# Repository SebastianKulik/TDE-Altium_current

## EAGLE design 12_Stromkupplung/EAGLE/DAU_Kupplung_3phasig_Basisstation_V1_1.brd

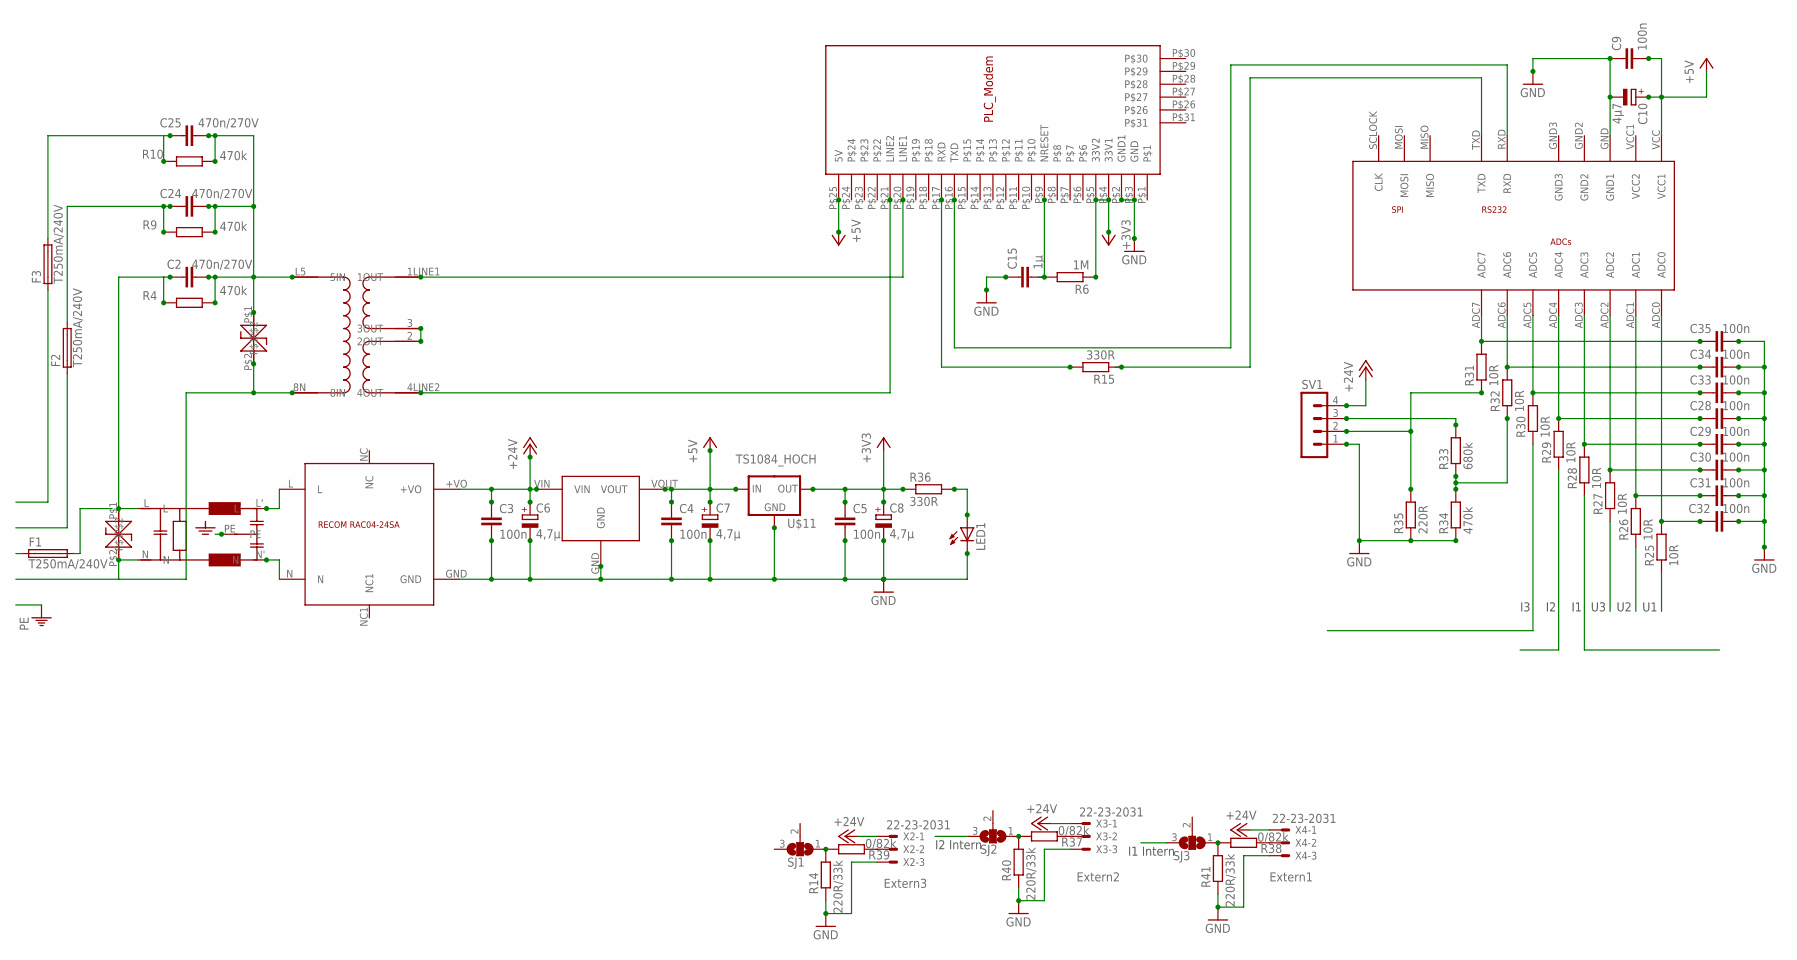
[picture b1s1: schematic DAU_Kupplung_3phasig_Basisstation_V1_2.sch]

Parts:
C2, C24, C25: 470n/270V; C225-087X268
C3, C4, C5, C9, C28, C29, C30, C31, C32, C33, C34, C35: 100n; C0805K
C6, C7, C8: 4,7µ; E2,5-6
C10: 4µ7; E2,5-6E
C15: 1µ; C0805K
F1, F2, F3: T250mA/240V; TR5
LED1: LEDSQR2X5; LED2X5
P6KE300CA: P6KE300CA; TSV
R4, R9, R10: 470k; 0204/7
R6: 1M; R0805
R14, R40, R41: 220R/33k; R0805
R15, R36: 330R; R0805
R25, R26, R27, R28, R29, R30, R31, R32: 10R; R0805
R33: 680k; R0805
R34: 470k; R0805
R35: 220R; R0805
R37, R38, R39: 0/82k; R0805
SJ1, SJ2, SJ3: SJ2WW; SJ_2W
SV1: MA04-1
TSV2: TSV
U$1: RECOM_RAC04_24SA; RAC04_12SA
U$3: ADUC831_MINIMUM; ADUC_MINIMUM
U$4: MODEMSTECKER; MODEM_FUSS
U$5: PLC_UEBERTRAGER_V2; PLC-UEBERTRAGER_V2
U$10: RECOM_785_05; RECOM785X
U$11: TS1084_HOCH
U$20: NETZFILTER_05_A; NETZFILTER
X2, X3, X4: 22-23-2031

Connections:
+3V3: C5.1, C8.+, R6.1, R36.1, U$4.P$4 (33V1), U$4.P$5 (33V2), U$11.OUT
+5V: C4.1, C7.+, C9.2, C10.+, U$3.VCC (VCC1), U$4.P$25 (5V), U$10.VOUT, U$11.IN
+12V: C3.1, C6.+, SV1.4, U$1.+VO, U$10.VIN, X2.1, X3.1, X4.1
ADC0: C32.1, R25.2, U$3.ADC0
ADC1: C31.1, R26.2, U$3.ADC1
ADC2: C30.1, R27.2, U$3.ADC2
ADC3: C29.1, R28.2, U$3.ADC3
ADC4: C28.1, R29.2, U$3.ADC4
ADC5: C33.1, R30.2, U$3.ADC5
GND: C3.2, C4.2, C5.2, C6.-, C7.-, C8.-, C9.1, C10.-, C15.1, C28.2, C29.2, C30.2, C31.2, C32.2, C33.2, C34.2, C35.2, LED1.K (C), R14.1, R34.1, R35.1, R40.1, R41.1, SV1.1, U$1.GND, U$3.GND (GND1), U$4.P$2 (GND1), U$4.P$3 (GND), U$10.GND, U$11.GND, X2.3, X3.3, X4.3
I1: R28.1, SJ3.2
I1INTERN: SJ3.3
I2: R29.1, SJ2.2
I2INTERN: SJ2.3
I3: R30.1, SJ1.2
L1: C2.1, F1.2, P6KE300CA.P$1, R4.2, U$20.L
L2: C24.1, F2.2, R9.2
L3: C25.1, F3.2, R10.2
N: P6KE300CA.P$2, TSV2.P$2, U$5.8N (8IN), U$20.N
unnamed: R15.2, U$4.P$17 (RXD)
unnamed: U$4.P$20 (LINE1), U$5.1LINE1 (1OUT)
unnamed: C35.1, R31.2, U$3.ADC7
unnamed: U$4.P$21 (LINE2), U$5.4LINE2 (4OUT)
unnamed: R15.1, U$3.TXD
unnamed: U$3.RXD, U$4.P$16 (TXD)
unnamed: U$1.L, U$20.L'
unnamed: LED1.A, R36.2
unnamed: C15.2, R6.2, U$4.P$9 (NRESET)
unnamed: C34.1, R32.2, U$3.ADC6
unnamed: C2.2, C24.2, C25.2, R4.1, R9.1, R10.1, TSV2.P$1, U$5.L5 (5IN)
unnamed: U$5.2 (2OUT), U$5.3 (3OUT)
unnamed: R33.2, SV1.3
unnamed: U$1.N, U$20.N'
unnamed: R37.2, R40.2, SJ2.1
unnamed: R37.1, X3.2
unnamed: R14.2, R39.2, SJ1.1
unnamed: R32.1, R33.1, R34.2
unnamed: R31.1, R35.2, SV1.2
unnamed: R39.1, X2.2
unnamed: R38.2, R41.2, SJ3.1
unnamed: R38.1, X4.2
PE: U$20.PE
U1: R25.1
U2: R26.1
U3: R27.1

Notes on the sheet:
Extern1
Extern2
Extern3
I1 Intern
I2 Intern

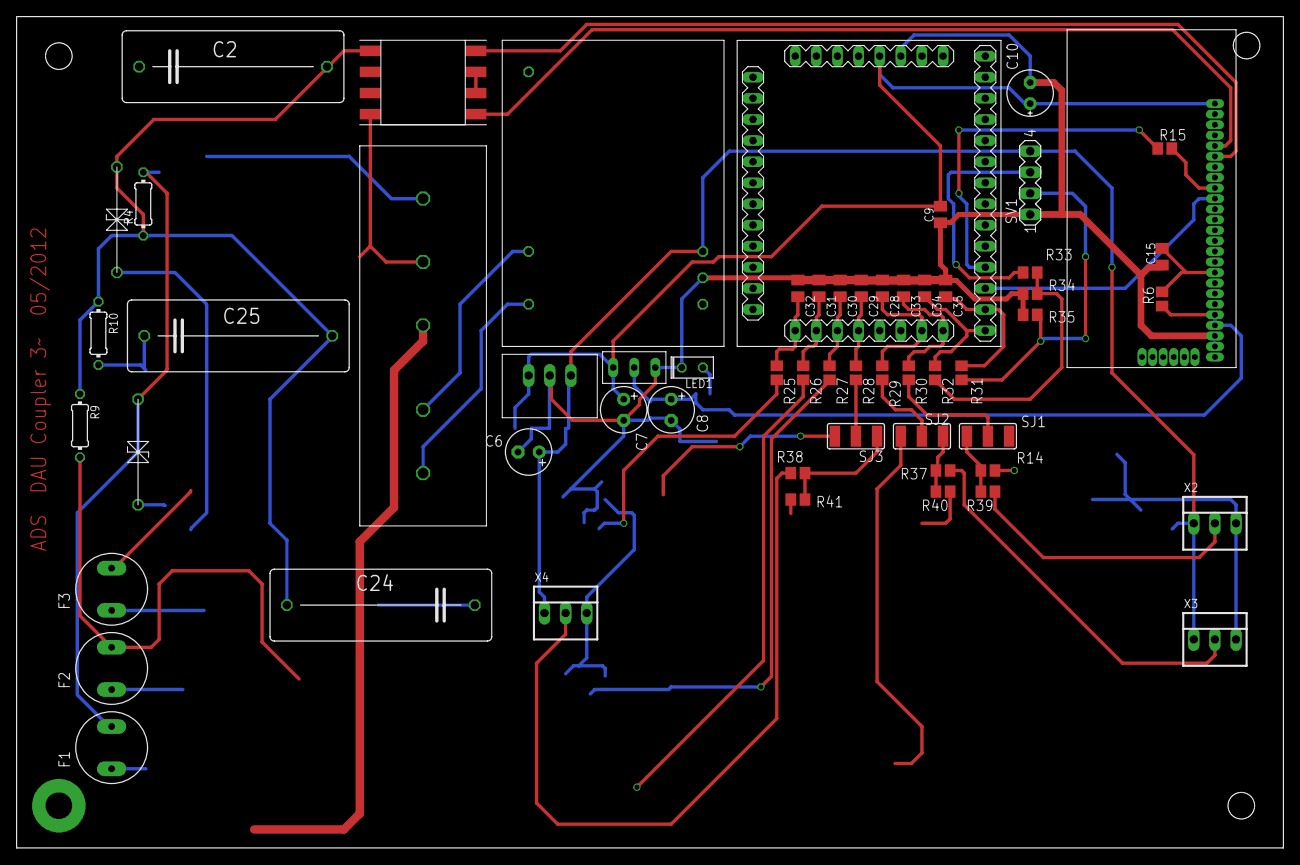
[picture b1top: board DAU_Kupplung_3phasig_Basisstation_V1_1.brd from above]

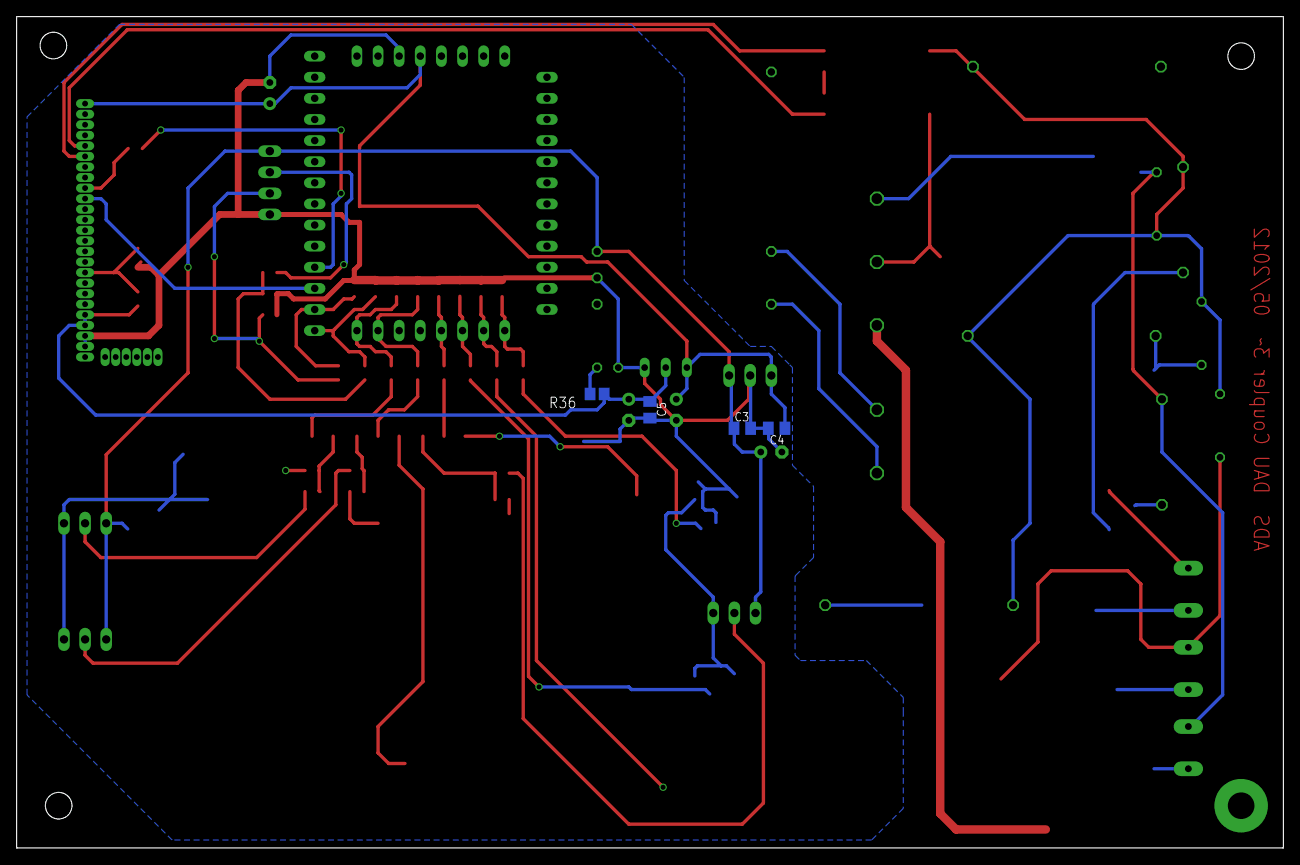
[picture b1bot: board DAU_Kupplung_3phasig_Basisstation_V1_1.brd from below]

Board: 2 copper layers, 152.4 x 100.0 mm, 63 parts (4 on the bottom side), 39 nets.

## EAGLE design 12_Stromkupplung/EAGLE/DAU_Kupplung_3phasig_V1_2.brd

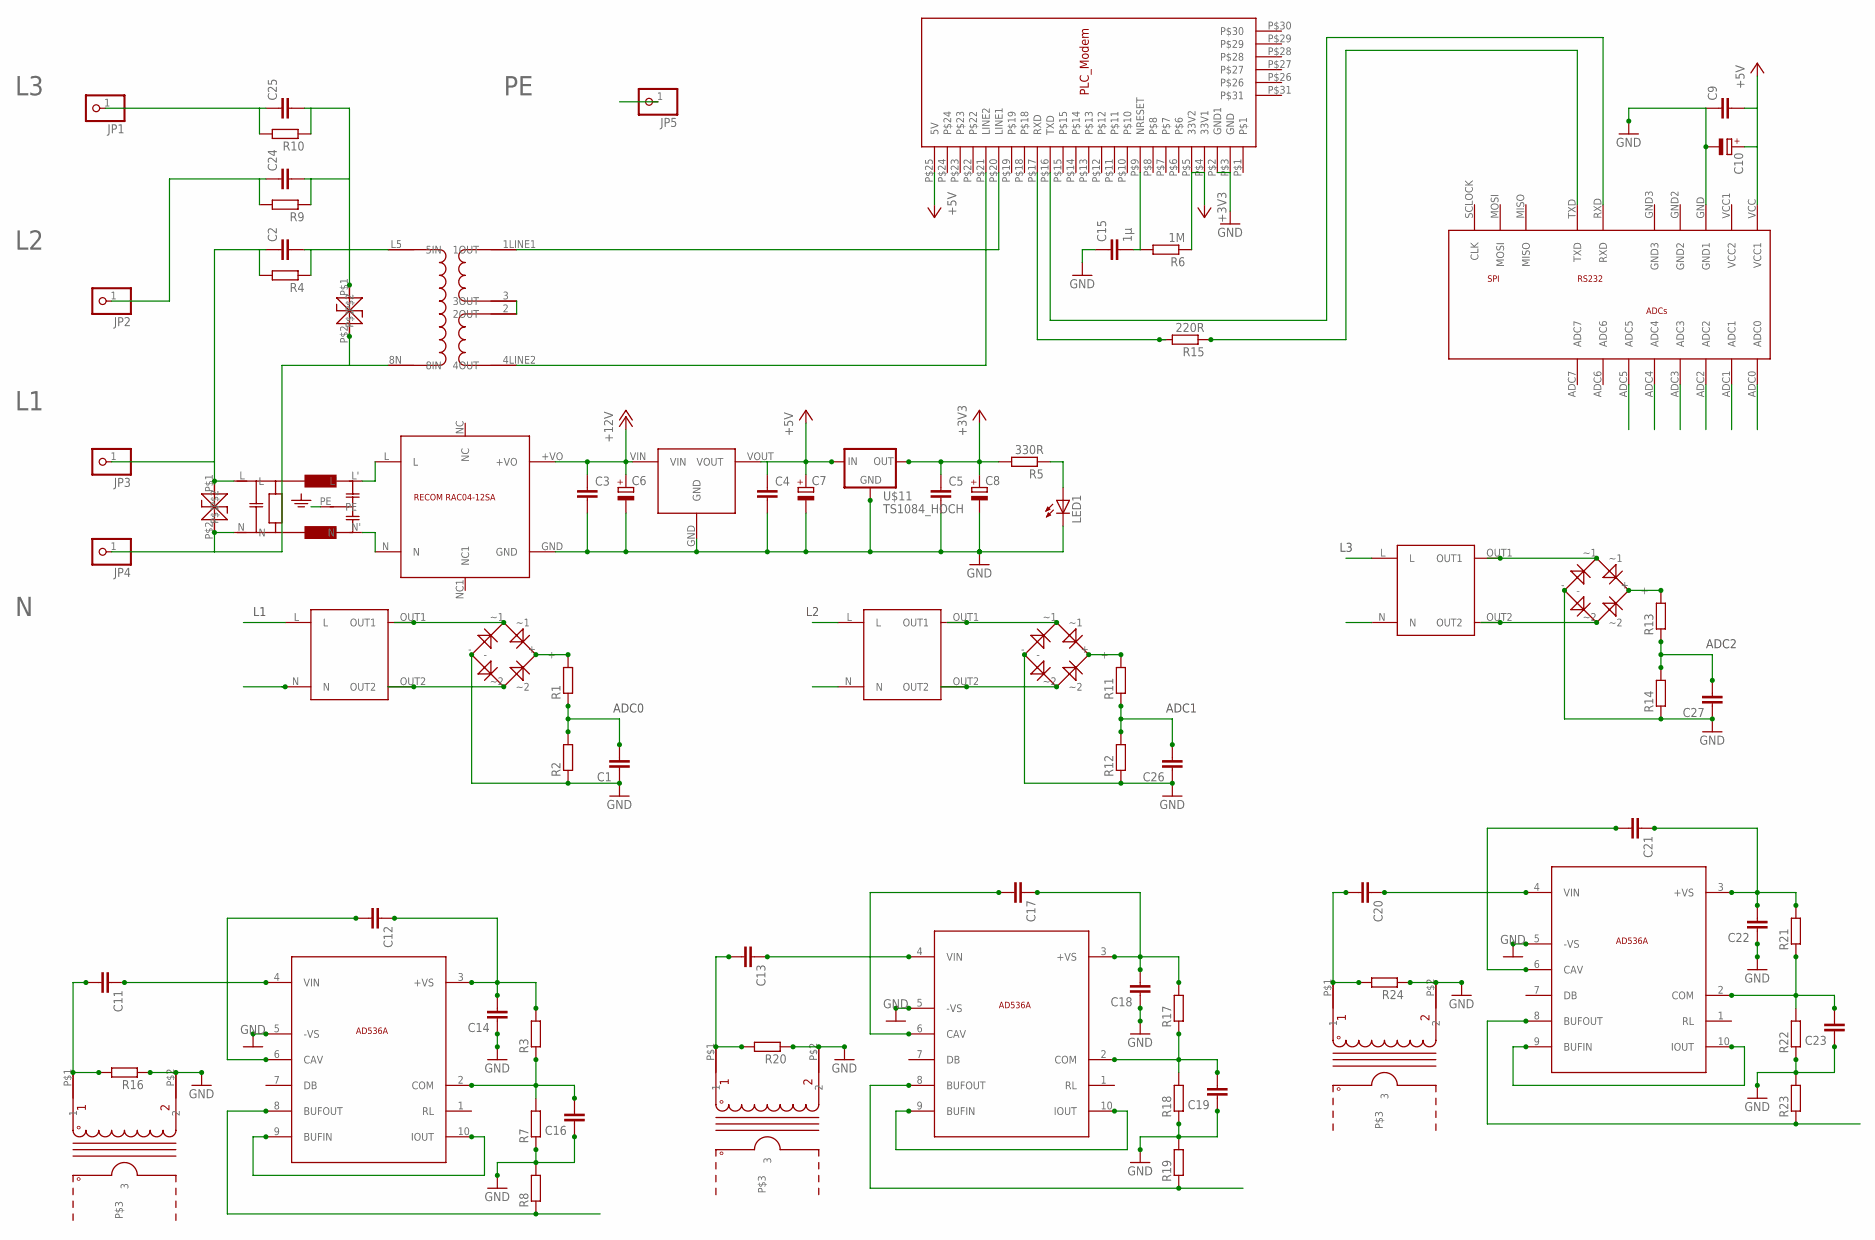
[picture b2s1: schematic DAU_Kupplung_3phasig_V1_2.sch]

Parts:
C1, C11, C12, C13, C14, C16, C17, C18, C19, C20, C21, C22, C23, C26, C27: C2,5-3; C2.5-3
C2, C24, C25: C-EU225-087X268; C225-087X268
C3, C4, C5, C9: C-EU025-040X050; C025-040X050
C6, C7, C8: CPOL-EUE2.5-6; E2,5-6
C10: CPOL-EUE2,5-6E; E2,5-6E
C15: 1µ; C025-040X050
JP1, JP2, JP3, JP4, JP5: PINHD-1X1; 1X01
LED1: LEDSQR2X5; LED2X5
R1, R2, R3, R4, R7, R8, R9, R10, R11, R12, R13, R14, R16, R17, R18, R19, R20, R21, R22, R23, R24: R-EU_0204/7; 0204/7
R5: 330R; 0204/7
R6: 1M; 0204/7
R15: 220R; 0204/7
TSV1, TSV2: TSV
U$1: RECOM_RAC04_12SA; RAC04_12SA
U$2, U$16, U$18: SICHERHEITSTRAFO; TRAFO_0,35VA
U$3: ADUC831_MINIMUM; ADUC_MINIMUM
U$4: MODEMSTECKER; MODEM_FUSS
U$5: PLC_UEBERTRAGER_V2; PLC-UEBERTRAGER_V2
U$6, U$7, U$14: AC1010
U$8, U$17, U$19: RECTIFIER
U$10: RECOM_785_05; RECOM785X
U$11: TS1084_HOCH
U$12, U$13, U$15: AD536; TO100_10PIN
U$20: NETZFILTER_05_A; NETZFILTER

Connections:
+3V3: C5.1, C8.+, R5.2, R6.1, U$4.P$4 (33V1), U$4.P$5 (33V2), U$11.OUT
+5V: C4.1, C7.+, C9.2, C10.+, U$3.VCC (VCC1), U$4.P$25 (5V), U$10.VOUT, U$11.IN
+12V: C3.1, C6.+, U$1.+VO, U$10.VIN
ADC0: C1.2, R1.1, R2.2, U$3.ADC0
ADC1: C26.2, R11.1, R12.2, U$3.ADC1
ADC2: C27.2, R13.1, R14.2, U$3.ADC2
ADC3: R8.1, U$3.ADC3, U$13.8 (BUFOUT)
ADC4: R19.1, U$3.ADC4, U$12.8 (BUFOUT)
ADC5: R23.1, U$3.ADC5, U$15.8 (BUFOUT)
GND: C1.1, C3.2, C4.2, C5.2, C6.-, C7.-, C8.-, C9.1, C10.-, C14.1, C15.1, C16.1, C18.1, C19.1, C22.1, C23.1, C26.1, C27.1, LED1.K (C), R2.1, R7.1, R8.2, R12.1, R14.1, R16.1, R18.1, R19.2, R20.1, R22.1, R23.2, R24.1, U$1.GND, U$3.GND (GND1), U$4.P$2 (GND1), U$4.P$3 (GND), U$6.P$2 (2), U$7.P$2 (2), U$8.-, U$10.GND, U$11.GND, U$12.5 (-VS), U$13.5 (-VS), U$14.P$2 (2), U$15.5 (-VS), U$17.-, U$19.-
L1: C2.1, JP3.1, R4.2, TSV1.P$1, U$2.L, U$20.L
L2: C24.1, JP2.1, R9.2, U$16.L
L3: C25.1, JP1.1, R10.2, U$18.L
N: JP4.1, TSV1.P$2, TSV2.P$2, U$2.N, U$5.8N (8IN), U$16.N, U$18.N, U$20.N
unnamed: R15.2, U$4.P$17 (RXD)
unnamed: C11.2, R16.2, U$6.P$1 (1)
unnamed: C11.1, U$13.4 (VIN)
unnamed: U$2.OUT1, U$8.~1
unnamed: U$4.P$20 (LINE1), U$5.1LINE1 (1OUT)
unnamed: U$13.9 (BUFIN), U$13.10 (IOUT)
unnamed: R1.2, U$8.+
unnamed: U$2.OUT2, U$8.~2
unnamed: R11.2, U$17.+
unnamed: U$16.OUT1, U$17.~1
unnamed: U$16.OUT2, U$17.~2
unnamed: U$4.P$21 (LINE2), U$5.4LINE2 (4OUT)
unnamed: R15.1, U$3.TXD
unnamed: U$3.RXD, U$4.P$16 (TXD)
unnamed: U$1.L, U$20.L'
unnamed: C16.2, R3.1, R7.2, U$13.2 (COM)
unnamed: C12.1, C14.2, R3.2, U$13.3 (+VS)
unnamed: LED1.A, R5.1
unnamed: C15.2, R6.2, U$4.P$9 (NRESET)
unnamed: C12.2, U$13.6 (CAV)
unnamed: C13.2, R20.2, U$7.P$1 (1)
unnamed: C13.1, U$12.4 (VIN)
unnamed: U$12.9 (BUFIN), U$12.10 (IOUT)
unnamed: C2.2, C24.2, C25.2, R4.1, R9.1, R10.1, TSV2.P$1, U$5.L5 (5IN)
unnamed: C19.2, R17.1, R18.2, U$12.2 (COM)
unnamed: C17.1, C18.2, R17.2, U$12.3 (+VS)
unnamed: C17.2, U$12.6 (CAV)
unnamed: C20.2, R24.2, U$14.P$1 (1)
unnamed: C20.1, U$15.4 (VIN)
unnamed: U$15.9 (BUFIN), U$15.10 (IOUT)
unnamed: U$5.2 (2OUT), U$5.3 (3OUT)
unnamed: R13.2, U$19.+
unnamed: U$18.OUT1, U$19.~1
unnamed: U$18.OUT2, U$19.~2
unnamed: C23.2, R21.1, R22.2, U$15.2 (COM)
unnamed: C21.1, C22.2, R21.2, U$15.3 (+VS)
unnamed: C21.2, U$15.6 (CAV)
unnamed: U$1.N, U$20.N'
PE: JP5.1, U$20.PE

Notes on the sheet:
ADC0
ADC1
ADC2

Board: 2 copper layers, 78 parts (0 on the bottom side), 53 nets, no tracks yet.

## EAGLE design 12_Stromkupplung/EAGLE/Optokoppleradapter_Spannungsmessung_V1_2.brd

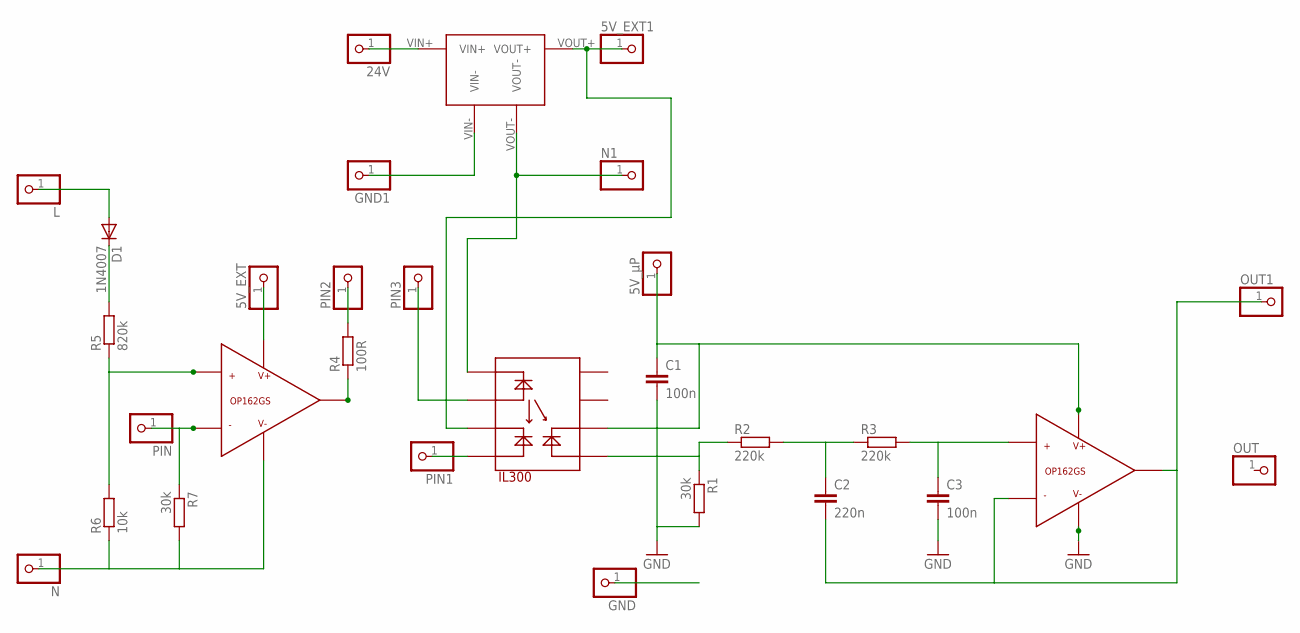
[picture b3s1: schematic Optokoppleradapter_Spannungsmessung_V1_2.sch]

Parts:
5V_EXT, 5V_EXT1, 5V_µP, 24V: PINHD-1X1; 1X01
C1, C3: 100n; C0805
C2: 220n; C0805
D1: 1N4007; DO35-7
GND, GND1: PINHD-1X1; 1X01
L: PINHD-1X1; 1X01
N, N1: PINHD-1X1; 1X01
OUT, OUT1: PINHD-1X1; 1X01
PIN, PIN1, PIN2, PIN3: PINHD-1X1; 1X01
R1: 30k; R0805
R2, R3: 220k; R0805
R4: 100R; R0805
R5: 820k; 0207/7
R6: 10k; 0207/7
R7: 30k; 0207/7
U$1: IL300; DIP8
U$2, U$3: OP162GS; SOIC_N
U$4: RECOM_RO-2405S; 4PIN_SIP

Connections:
5V_EXTERN: 5V_EXT.1, U$2.P$7 (V+)
5V_EXTERN1: 5V_EXT1.1, U$1.P$3, U$4.VOUT+
5V_µP: 5V_µP.1, C1.1, U$1.P$6, U$3.P$7 (V+)
24V: 24V.1, U$4.VIN+
GND: GND.1
GND1: C1.2, C3.2, GND1.1, R1.2, U$3.P$4 (V-), U$4.VIN-
L: D1.A, L.1
N: N.1, R6.1, R7.2, U$2.P$4 (V-)
N1: N1.1, U$1.P$1, U$4.VOUT-
unnamed: D1.C, R5.2
unnamed: R5.1, R6.2, U$2.P$3 (+)
unnamed: PIN1.1, U$1.P$4
unnamed: PIN.1, R7.1, U$2.P$2 (-)
unnamed: R4.1, U$2.P$6 (OUT)
unnamed: PIN2.1, R4.2
unnamed: PIN3.1, U$1.P$2
unnamed: R1.1, R2.1, U$1.P$5
unnamed: C2.1, R2.2, R3.1
unnamed: C3.1, R3.2, U$3.P$3 (+)
OUT1: C2.2, OUT1.1, U$3.P$2 (-), U$3.P$6 (OUT)

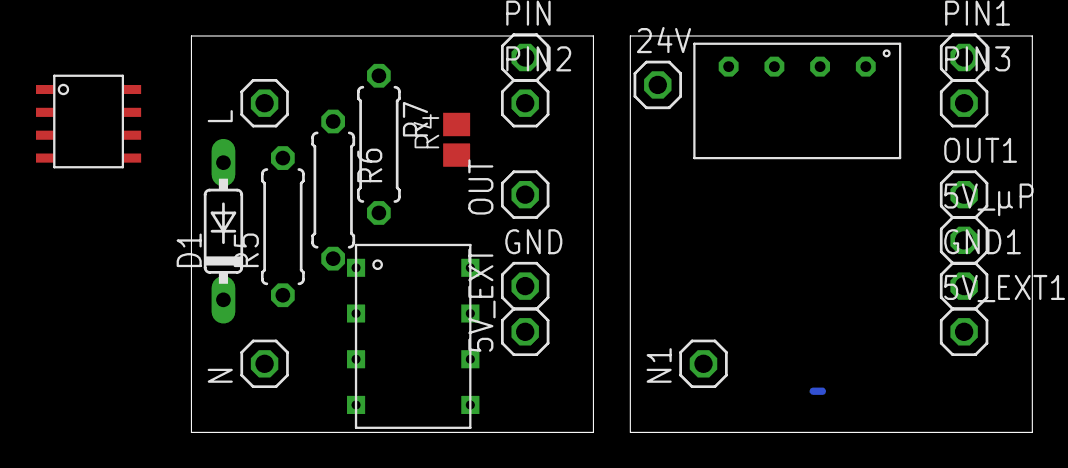
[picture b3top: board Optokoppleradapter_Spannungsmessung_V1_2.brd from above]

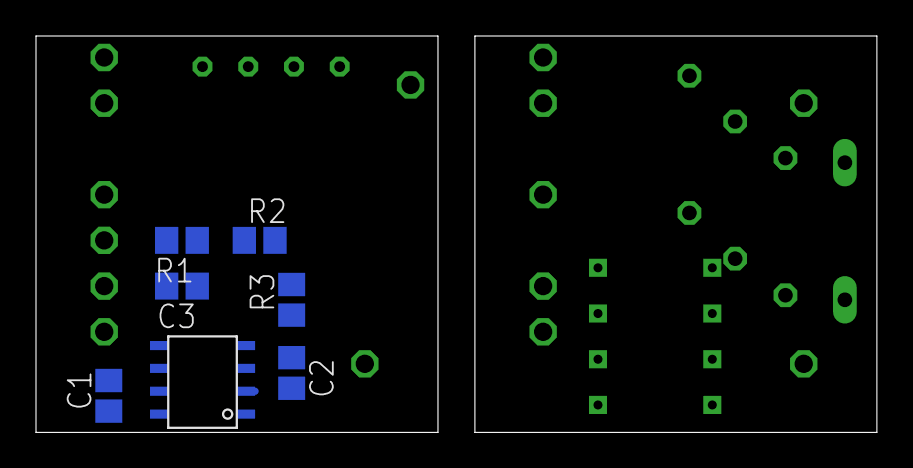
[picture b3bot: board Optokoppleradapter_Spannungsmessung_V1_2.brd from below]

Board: 2 copper layers, 46.7 x 22.0 mm, 30 parts (7 on the bottom side), 19 nets.
